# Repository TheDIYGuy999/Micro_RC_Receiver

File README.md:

# This is an ATMEL Mega328P / NRF24L01+ based 2.4GHz radio receiver
## Features:
- Compatible with this transmitter: https://github.com/TheDIYGuy999/RC_Transmitter
- Programmable with Arduino IDE
- 4 RC servo connectors
- SBUS output
- Outputs for Headlights, indicators, taillights with brake lights
- Additional switching output
- Support for self balancing robot or car with stability control (using an MPU-6050 sensor)
- Integrated TB6612FNG dual dc motor driver
- Serial header (with SBUS support)
- I2C header (for example for the supported MPU-6050)
- ICSP header for programming with Arduino IDE (use "TheDIYGuy999 328P" board definition and set brownout voltage to 1.8V)
- NRF24L01+ SMD module integrated
- very small size
- Up to 20 vehicle addresses selectable, allows to use the same remote controller for 10 vehicles
- Eagle & Gerber files are also provided, if you want to build your own receiver!

See: https://www.youtube.com/playlist?list=PLGO5EJJClJBCjIvu8frS7LrEU3H2Yz_so

New in V 1.3:
- Vehicle configuration is now stored in "vehicleConfig.h", so the main code always stays the same.
- Crude frequency hopping, if bad receiving quality is detected (needs to be improved).

New in V 1.4:
- 10 vehicle addresses instead of 5
- More vehicle configuration options
- The "BACK" button on the transmitter can now be used (if the menu screen is not displayed on the OLED) as a momentary button, for example for a horn on the vehicle. It is sent as "data.momentary1"
- SimpleTimer library replaced with my own code, which uses significantly less memory

New in V 1.5:
- Added steering mixer for semi caterpillar and caterpillar vehicles such as tanks, diggers etc.
- Channel 3 is throttle, channel 1 is steering
- More vehicle configuration options in vehicleVonfig.h
- The left caterpillar is motor 2, the right is motor 1
- Steering servo 1 can be used in parallel (for semi caterpillar vehicles or vehicles with electronic differential)

New in V 1.6:
- Added indicator lights - wired to A4 (SDA) / A5 (SCL) ports
- enabled and disabled left / right by channel 4 left / right
- disabled by turning back the steering wheel (channel 1) - just like a real car
- hazard lights (all indicators flashing), if no connection to the transmitter

New in V 1.61:
- Battery cutoff bug fixed

New in V 1.7 (Support for board revision 1.3):
- **** TB6612FNG library update to V1.1 is required! ****
- motor driver pinout has changed in board V1.3. So we are now able to adjust the PWM frequency of motor2. This allows smooth motor operation without the typical PWM whining.
- vehicleConfig.h changed: "boardVersion" and "HP" variables added. They allow to stay compatible with older board versions. Just select the correct configuration.
- The new "HP" (High Power) board version has only one motor driver channel, because both TB6612FNG channels are wired in parallel. It's able to supply 2.4A (average) / 6.4A (peak) so we can use bigger motors. This is useful for models, which use a steering servo and don't need a second motor channel.'
- automatic radio re-initialisation after signal timeout

New in V 1.71
- Battery monitoring and cutoff triggering improved. Under load, 0.3V are now added to the battery voltage to compensate the voltage drop. This allows to set the cutoff voltage to 3.6V, even with bigger loads.
- Vehicle #7 added.

New in V 1.8
- New "engineSound" variable in "vehicleconfig.h". True means, that the servo 3 pulse signal can be switched on and off, using the  channel 2 joystick. This switches the engine sound on my "Rc Engine Sound" unit on and off.

New in V 1.9
- New vehicle specific configuration section in vehicleConfig.h. The configuration is now done entirely during compilation time.

New in V 2.0
- vehicle Config.h: New vehicleType 3 (forklift) added. Motor 2 is used as lifting motor in this case. A servo is required as steering motor.
- Beacon lights can be wired to servo channel 4. Select "beacons = true" in this case. The beacons are flashing during vehicle movement and are switching off, after the vehicle did not move for 10s.

New in V 2.1
- Sounds for a STAR WARS R2-D2 robot can now be generated on servo channel 3
- "toneOut" variable added to vehicleConfig.h. True means, that servo 3 channel is generating sounds instead of a servo signal.
- Do not enable "toneOut" and "engineSound" at the same time.
- Note: the Arduino tone() function is blocking. So don't play sounds while driving ;-)

New in V 2.2
- **** TB6612FNG library update to V1.2 is required! **** https://github.com/TheDIYGuy999/TB6612FNG
- **** The PID library is required! **** https://github.com/br3ttb/Arduino-PID-Library/
- Support for self balancing (inverted pendulum, segway) vehicles. See: https://www.youtube.com/watch?v=zse9-l2Yo3Y)
- A MPU-6050 accelerometer & gyro module is used for the balancing data communication via SDA & SCL
- Note, that the receiver will not work, if your vehicleType is 4 (balancing) and no MPU-6050 is connected!
- Do not enable "balancing" and "indicators" at the same time.

New in V 2.21
- Gyro drift calibration bug fixed
- Changed the balancing controller refresh rate to 125Hz to reduce jitter on a 8MHz MCU. Reason: one program loop takes 4 - 7ms, so we can't use a time base of 4ms (=250Hz).

New in V 2.3
- MRSC (Micro RC Stability Control) added. This functionality is similar to the Traxxas TSM or ESC. See: https://www.youtube.com/watch?v=IPve7QpdLBc&t=5s
- The steering servo angle is compensated in accordance with the speed, the requested steering angle and the measured yaw rate, which is coming from the MPU-6050
- Basically the mrsc() function was added. The required yaw rate is already calculated in the balancing.h, which is already existing for self balancing robots
- If you want to use this functionality, you have to set the vehicleType to 5 in the vehicleConfig.h. Please note, that the receiver will not work, if no MPU-6050 is connected and the vehicleType is set to 4 or 5!

New in V 2.31
 - MRSC gain factor now depending on the potentiometer 1 value on the transmitter
 - Allows to fine adjust the MRSC during driving, depending on the requirements of the street surface
 - Note, that you need to connect a potentiometer to the analog input A6 of your transmitter!
 
 New in V 2.32
 - Flickering headlights bug in vehicleType 5 fixed
 - The accelerometer vectors are not processed anymore in vehicleType 5. This is only required for the self balancing robot (vehicleType 4)
 
 New in V 2.4
 - The I2C bus is scanned for an MPU-6050 sensor during the setup() sequence. The vehicleType is automatically changed to 0 (car without MRSC), if no sensor is detected.
 - This means, that a car with vehicleType 5 (MRSC Stability Control) can now also be used without an MPU-6050 plugged in.
 - Note, that the self balancing mode (vehicleType 4) always requires an MPU-6050. Otherwise the receiver will not start.
 
 New in V 2.41
 - The "indicators" variable is now locked and can't be enabled, if the SDA and SCL pins are in use for the MPU-6050 sensor. This is the case in vehicleMode 4 and 5.
 
 New in V 2.5
 - The MRSC stability control is now also working for cars without a steering servo
 - Code was added to control a DC steering motor (as found in cheap RC cars) in accordance with the MPU-6050 yaw rate
 - This is for example very useful for Coke Can Cars. See: https://www.youtube.com/watch?v=jr5yYBal3vk
 
 New in V 2.6
 - The MRSC stability control can now be used with transmitters without gain adjustment potentiometer
 - The following optional parameters in the vehicleConfig.h allow to use a fixed gain: MRSC_FIXED, mrscGain
 - Allows to add an MPU-6050 gyro to every vehicle. So we always have a closed loop steering control, even without a proper servo with potentiometer feedback
 - On the "Non-High-Power" receiver model, 0.3V battery voltage are not added anymore during driving. This is not useful, if there is not much current draw.
 
 New in V 2.7
 - The MRSC stability control gain adjustment knob can now be linked to servo CH4, if "potentiometer1" is set to "true" in vehicleConfig.h
 - This is useful, if an external MRSC stability control unit for 3 pin servos is used. See: https://github.com/TheDIYGuy999/MRSC_Adapter_3Pin_Servo
 - Servo CH4 is wired to pin 5 in this case. This allows to adjust the MRSC gain on the transmitter, just as with the internal MRSC stability control
 
 New in V 2.8
 - Added support for differential thrust controlled airplanes
 - Tested with a Piper J3 CUB from Banggood
 
 New in V 2.9
 - Added TWO_SPEED_GEARBOX option for mechanical two speed gearboxes, shifted by a servo, connected to CH2, controlled by "Mode 1" button
 - Example see vehicle CONFIG_WPL_B-36
 - See video: https://www.youtube.com/watch?v=EaOJE_GU5pk&t=1s
 
 New in V 3.0
 - Added TRACTOR_TRAILER_UNLOCK option. Used to operate the tractor trailer unlocking servo
 - Press the "Back / Pulse" button to unlock your trailer
 - See vehicle "CONFIG_JJRC_Q60" for example
 - Parts for 3D printing: https://www.thingiverse.com/thing:3399449
 
 New in V 3.1
 - Added THRE_SPEED_GEARBOX option for mechanical three speed gearboxes, shifted by a servo, connected to CH2, controlled by a 3 position switch, connected to CH2 Joystick input of the transmitter. A 10k resistor is reqired between GND and the input pin as well as between the input pin and VCC
 - Three individual servo positions can be programmed: lim2L, lim2C, lim2R
 - Example see vehicle CONFIG_HG_P407
 
 New in V 3.2
 - Added the "TXO_toggle1" variable: allows to toggle the TXO pin, using the "Back / Impulse" button on the transmitter
 - Useful for example for additional lights
 - Don't activate it in combination with "TXO_momentary1". Serial is not usable, if one of these booleans is set to true
 
 New in V 3.3
 - Added experimental support for serial communication with my "Arduino RC engine sound generator for ESP32": https://github.com/TheDIYGuy999/Rc_Engine_Sound_ESP32
 - Uncomment "#define SERIAL_COMMUNICATION" in Adjustments.h of the sound generator
 - Connect pin 36 "VP"of the sound generator  to pin "TXO" of the receiver (disable "TXO_momentary1", "TXO_toggle1" & "headLights" in vehicleConfig.h)
 
 New in V 3.31
 - "headlLights" must be inactive as well in order to use serial communication!
 
 New in V 3.32
 - "data.pot1" properly initialized (cauesd an issue on the ESP32 engine sound generator)
 
 New in V 3.4
 - SBUS support added (variable "SBUS_SERIAL" in vehicleConfiguration.h
 - Channel order and comments see sendSbusCommands()
 - You need to install my SBUS library: https://github.com/TheDIYGuy999/SBUS
 - Connect your servos or what ever to pin "TXO"  (disable "TXO_momentary1", "TXO_toggle1" & "headLights" in vehicleConfig.h)
 
 New in V 3.5
 - mode1, mode2 and momentary1 properly initialised before SBUS is enabled
 
 New in V 3.6
 - "vehicleType" 1 or 2 (tracked or half tracked mode steering mixer) is now working as well, if two ESC are connected to servo pins 2 and 3. In the past, it was only usable with the internal TB6612 dual DC motor driver.
 - Also works in combination with my ESP32 Engine Sound & Light Controller (SBUS & PWM Mode)
 
 New in V 3.7
 - Steering center position separately adjustable, using "#define STEERING_3_POINT_CAL" and "lim1C". This is useful for badly designed steering linkage geometries. Example see vehicle configuration "CONFIG_WPL_B_36_MODE1"
 
 New in V 3.8:
 - 20 vehicle addresses instead of 10
 - Less RAM usage
 - 2 speed transmission not shifting while standing still. This will protect the shifting servo.

New in V 3.81:
 - Libraries comments added
 
 New in V 3.9:
 - New "#define VEHICLE_TYPE_3_WITH_ESC" option for vehicle type 3. Allows to use both TB6612 FNG motor driver channels for other stuff
 - Used in "CONFIG_MECCANO_DUMPER"

## Usage

See pictures

Newest version v1.5:

First prototype:

Receiver PCB

MPU-6050 shield PCB

(c) 2016 - 2020 TheDIYGuy999

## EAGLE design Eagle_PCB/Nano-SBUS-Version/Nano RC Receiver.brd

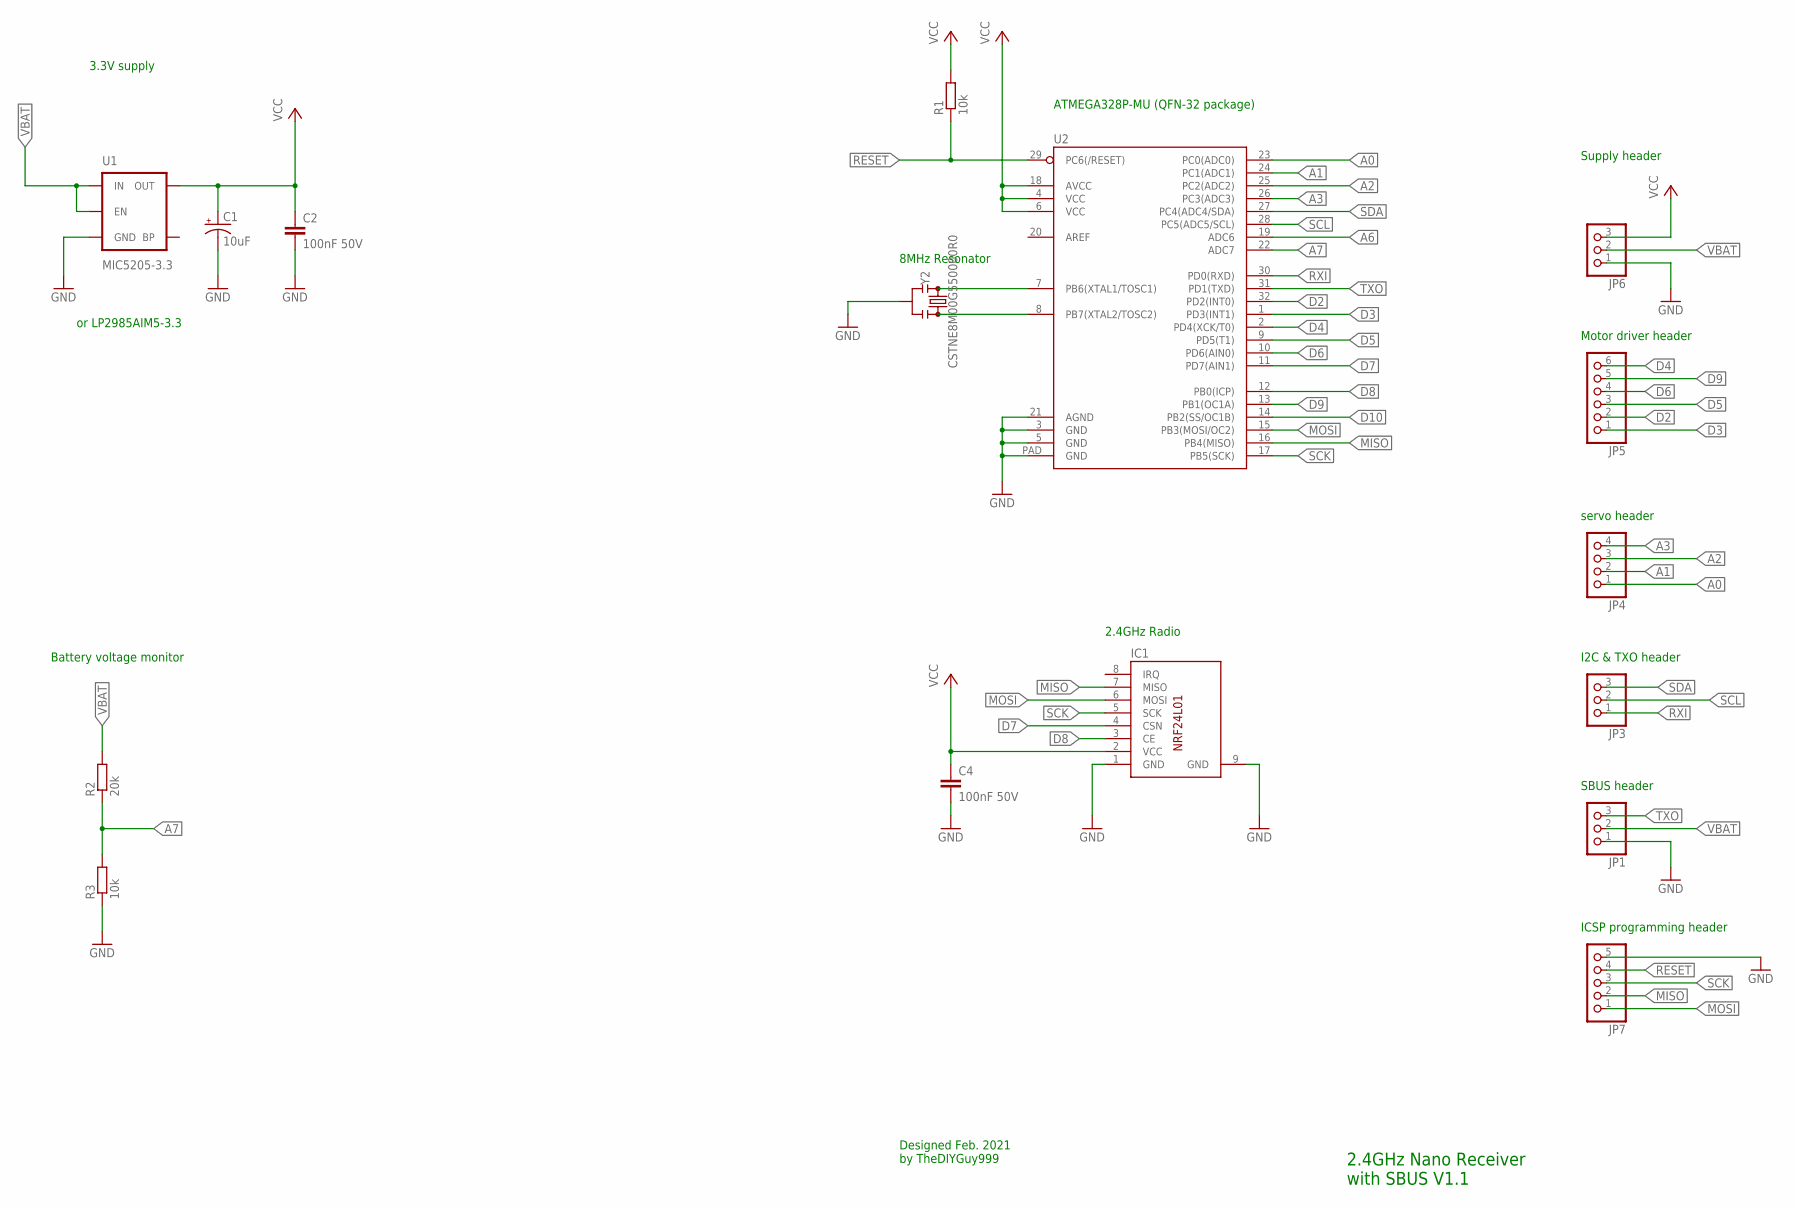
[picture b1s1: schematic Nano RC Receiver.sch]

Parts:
C1: 10uF; EIA3216
C2, C4: 100nF 50V; C0603
IC1: NRF24L01SMD_PAD; NRF24L01_SMD_PAD
JP1: PINHD-1X3SMT; 1X03_SMT
JP3, JP6: PINHD-1X31.27; 1X03_1.27
JP4: PINHD-1X41.27; 1X04_1.27
JP5: PINHD-1X61.27; 1X06_1.27
JP7: PINHD-1X51.27; 1X05_1.27
R1, R3: 10k; R0603
R2: 20k; R0603
U1: MIC5205-3.3; SOT23-5
U2: ATMEGA328P_MLFMLF32; MLF32-PAD
Y2: CSTNE8M00G550000R0; RESONATOR-SMD-3.2X1.3

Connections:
A0: JP4.1, U2.23 (PC0(ADC0))
A1: JP4.2, U2.24 (PC1(ADC1))
A2: JP4.3, U2.25 (PC2(ADC2))
A3: JP4.4, U2.26 (PC3(ADC3))
A6: U2.19 (ADC6)
A7: R2.1, R3.2, U2.22 (ADC7)
D2: JP5.2, U2.32 (PD2(INT0))
D3: JP5.1, U2.1 (PD3(INT1))
D4: JP5.6, U2.2 (PD4(XCK/T0))
D5: JP5.3, U2.9 (PD5(T1))
D6: JP5.4, U2.10 (PD6(AIN0))
D7: IC1.4 (CSN), U2.11 (PD7(AIN1))
D8: IC1.3 (CE), U2.12 (PB0(ICP))
D9: JP5.5, U2.13 (PB1(OC1A))
D10: U2.14 (PB2(SS/OC1B))
GND: C1.C (-), C2.2, C4.2, IC1.1 (GND), IC1.9 (GND), JP1.1, JP6.1, JP7.5, R3.1, U1.2 (GND), U2.3 (GND), U2.5 (GND), U2.21 (AGND), U2.PAD (GND), Y2.2
MISO: IC1.7 (MISO), JP7.2, U2.16 (PB4(MISO))
MOSI: IC1.6 (MOSI), JP7.1, U2.15 (PB3(MOSI/OC2))
RESET: JP7.4, R1.1, U2.29 (PC6(/RESET))
RXI: JP3.1, U2.30 (PD0(RXD))
SCK: IC1.5 (SCK), JP7.3, U2.17 (PB5(SCK))
SCL: JP3.2, U2.28 (PC5(ADC5/SCL))
SDA: JP3.3, U2.27 (PC4(ADC4/SDA))
TOSC1: U2.7 (PB6(XTAL1/TOSC1)), Y2.1
TOSC2: U2.8 (PB7(XTAL2/TOSC2)), Y2.3
TXO: JP1.3, U2.31 (PD1(TXD))
VBAT: JP1.2, JP6.2, R2.2, U1.1 (IN), U1.3 (EN)
VCC: C1.A (+), C2.1, C4.1, IC1.2 (VCC), JP6.3, R1.2, U1.5 (OUT), U2.4 (VCC), U2.6 (VCC), U2.18 (AVCC)

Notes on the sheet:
3.3V supply
2.4GHz Radio
2.4GHz Nano Receiver with SBUS V1.1
Designed Feb. 2021 by TheDIYGuy999
8MHz Resonator
or LP2985AIM5-3.3
Battery voltage monitor
ICSP programming header
servo header
SBUS header
I2C & TXO header
Motor driver header
Supply header
ATMEGA328P-MU (QFN-32 package)

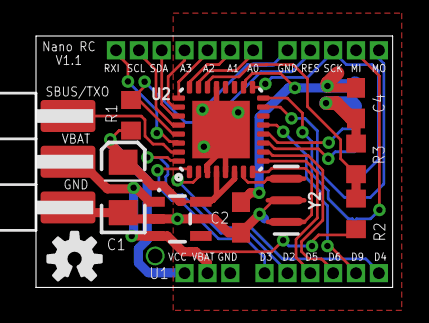
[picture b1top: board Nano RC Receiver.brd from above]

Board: 2 copper layers, 19.8 x 14.0 mm, 17 parts (1 on the bottom side), 26 nets.

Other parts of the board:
LOGO2: OSHW-LOGOS; OSHW-LOGO-S

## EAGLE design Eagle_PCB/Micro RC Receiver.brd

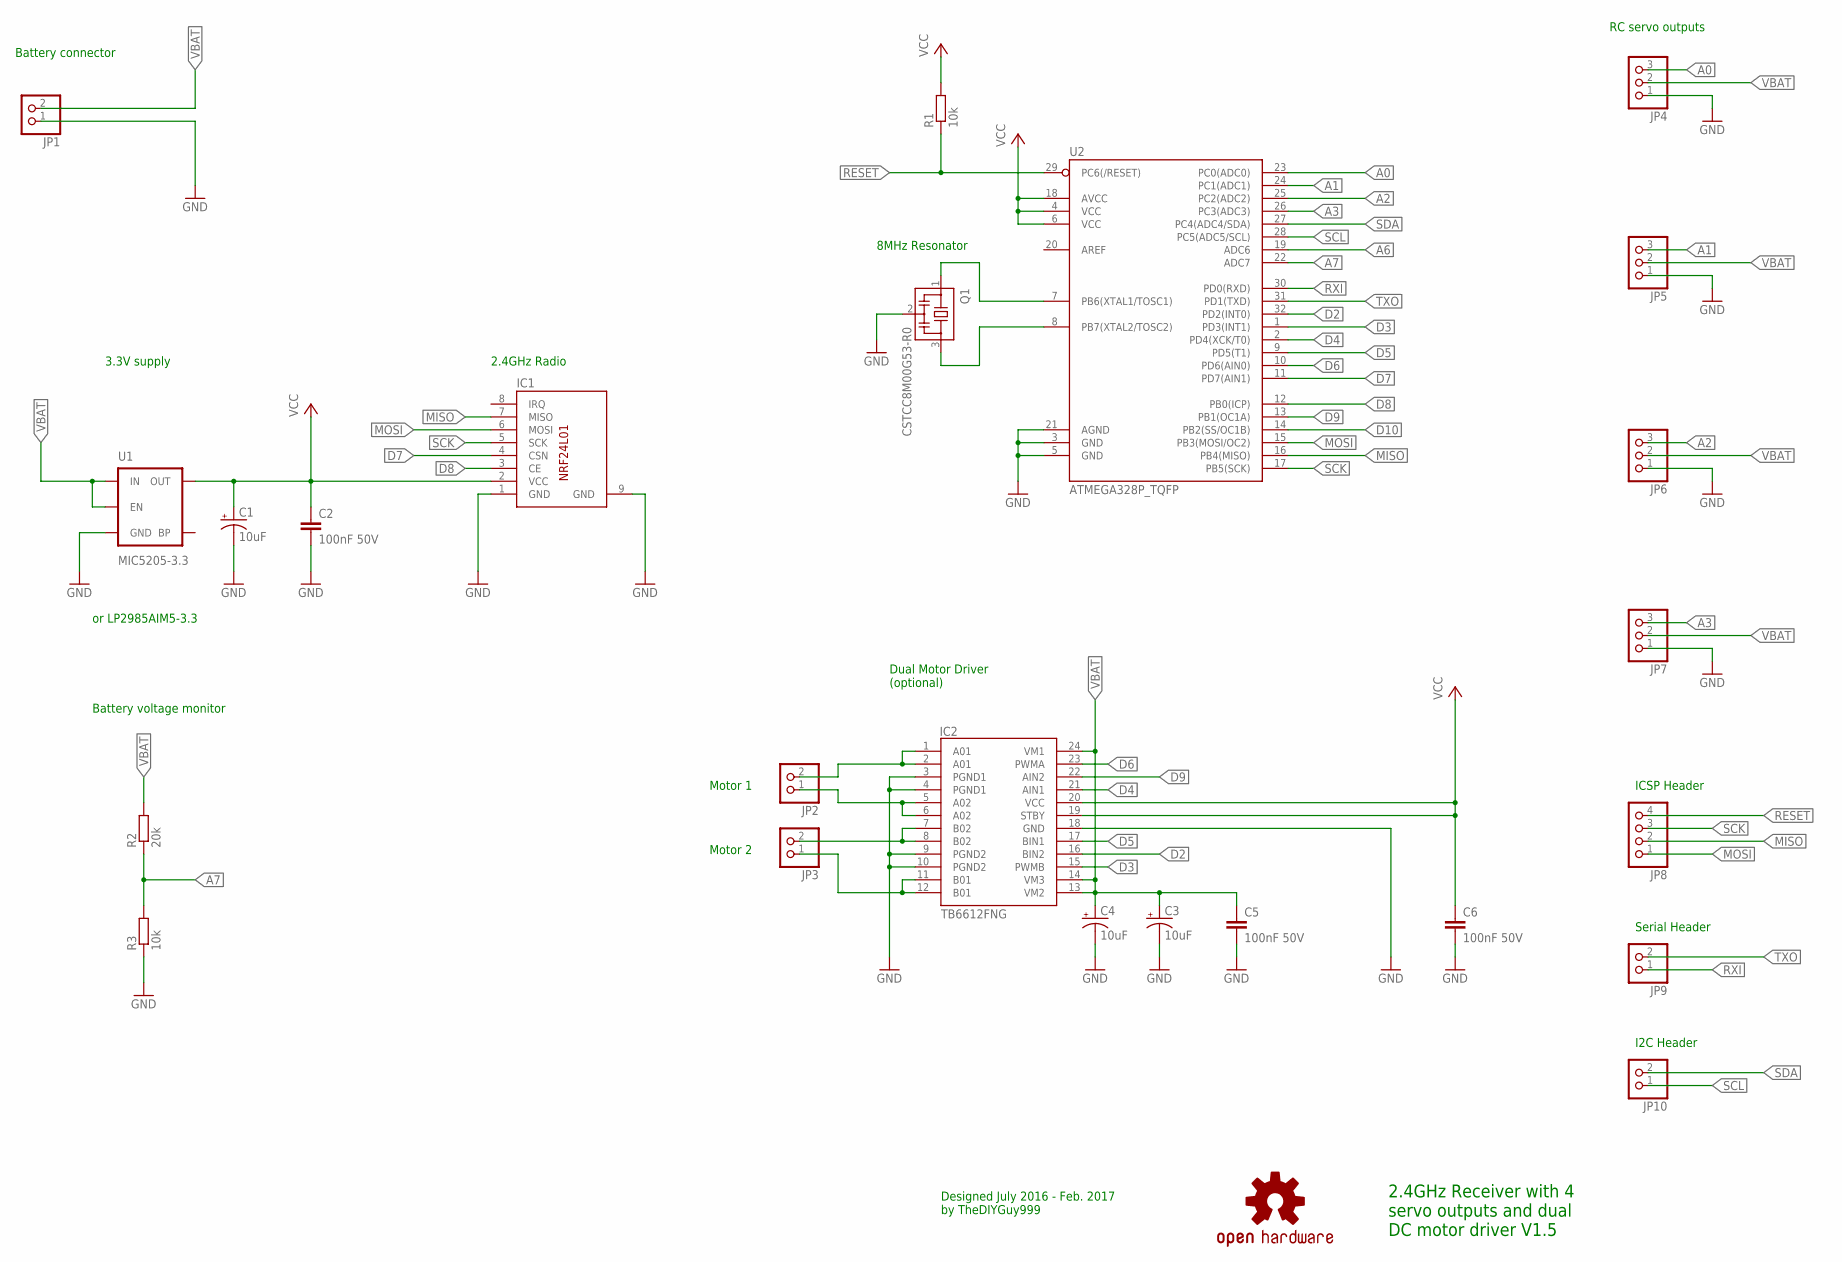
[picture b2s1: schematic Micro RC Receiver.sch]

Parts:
C1, C3, C4: 10uF; EIA3216
C2, C5, C6: 100nF 50V; C0805
IC1: NRF24L01SMD; NRF24L01_SMD
IC2: TB6612FNG; SSOP24
JP1, JP2, JP3, JP9, JP10: PINHD-1X2; 1X02
JP4, JP5, JP6, JP7: PINHD-1X3; 1X03
JP8: PINHD-1X4; 1X04
LOGO1: OSHW-LOGOS; OSHW-LOGO-S
Q1: CSTCC8M00G53-R0; CSTCC
R1, R3: 10k; R0805
R2: 20k; R0805
U1: MIC5205-3.3; SOT23-5
U2: ATMEGA328P_TQFP; TQFP32-08

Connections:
A0: JP4.3, U2.23 (PC0(ADC0))
A1: JP5.3, U2.24 (PC1(ADC1))
A2: JP6.3, U2.25 (PC2(ADC2))
A3: JP7.3, U2.26 (PC3(ADC3))
A6: U2.19 (ADC6)
A7: R2.1, R3.2, U2.22 (ADC7)
D2: IC2.16 (BIN2), U2.32 (PD2(INT0))
D3: IC2.15 (PWMB), U2.1 (PD3(INT1))
D4: IC2.21 (AIN1), U2.2 (PD4(XCK/T0))
D5: IC2.17 (BIN1), U2.9 (PD5(T1))
D6: IC2.23 (PWMA), U2.10 (PD6(AIN0))
D7: IC1.4 (CSN), U2.11 (PD7(AIN1))
D8: IC1.3 (CE), U2.12 (PB0(ICP))
D9: IC2.22 (AIN2), U2.13 (PB1(OC1A))
D10: U2.14 (PB2(SS/OC1B))
GND: C1.C (-), C2.2, C3.C (-), C4.C (-), C5.2, C6.2, IC1.1 (GND), IC1.9 (GND), IC2.3 (PGND1), IC2.4 (PGND1), IC2.9 (PGND2), IC2.10 (PGND2), IC2.18 (GND), JP1.1, JP4.1, JP5.1, JP6.1, JP7.1, Q1.2, R3.1, U1.2 (GND), U2.3 (GND), U2.5 (GND), U2.21 (AGND)
MISO: IC1.7 (MISO), JP8.2, U2.16 (PB4(MISO))
MOSI: IC1.6 (MOSI), JP8.1, U2.15 (PB3(MOSI/OC2))
unnamed: Q1.3, U2.8 (PB7(XTAL2/TOSC2))
unnamed: Q1.1, U2.7 (PB6(XTAL1/TOSC1))
unnamed: IC2.11 (B01), IC2.12 (B01), JP3.1
unnamed: IC2.7 (B02), IC2.8 (B02), JP3.2
unnamed: IC2.5 (A02), IC2.6 (A02), JP2.1
unnamed: IC2.1 (A01), IC2.2 (A01), JP2.2
RESET: JP8.4, R1.1, U2.29 (PC6(/RESET))
RXI: JP9.1, U2.30 (PD0(RXD))
SCK: IC1.5 (SCK), JP8.3, U2.17 (PB5(SCK))
SCL: JP10.1, U2.28 (PC5(ADC5/SCL))
SDA: JP10.2, U2.27 (PC4(ADC4/SDA))
TXO: JP9.2, U2.31 (PD1(TXD))
VBAT: C3.A (+), C4.A (+), C5.1, IC2.13 (VM2), IC2.14 (VM3), IC2.24 (VM1), JP1.2, JP4.2, JP5.2, JP6.2, JP7.2, R2.2, U1.1 (IN), U1.3 (EN)
VCC: C1.A (+), C2.1, C6.1, IC1.2 (VCC), IC2.19 (STBY), IC2.20 (VCC), R1.2, U1.5 (OUT), U2.4 (VCC), U2.6 (VCC), U2.18 (AVCC)

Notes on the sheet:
Motor 2
Motor 1
Dual Motor Driver (optional)
Battery connector
3.3V supply
2.4GHz Radio
RC servo outputs
2.4GHz Receiver with 4 servo outputs and dual DC motor driver V1.5
Designed July 2016 - Feb. 2017 by TheDIYGuy999
Serial Header
ICSP Header
I2C Header
8MHz Resonator
or LP2985AIM5-3.3
Battery voltage monitor

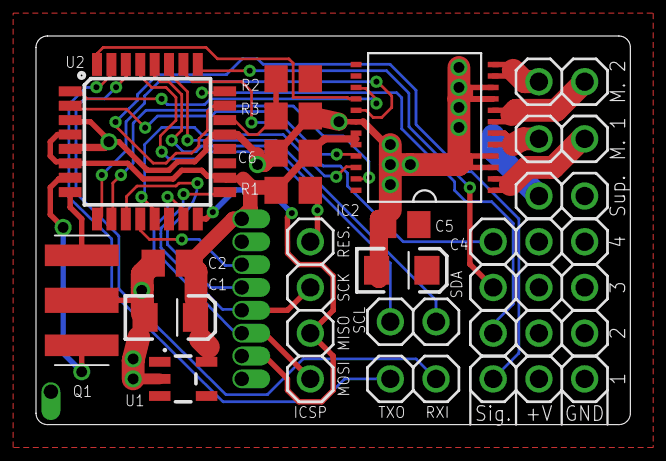
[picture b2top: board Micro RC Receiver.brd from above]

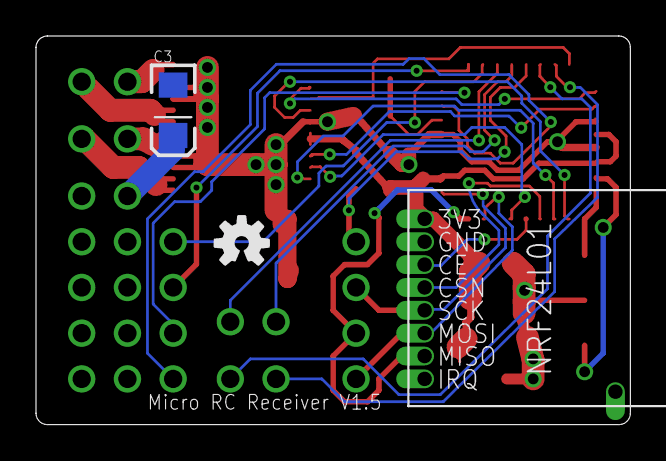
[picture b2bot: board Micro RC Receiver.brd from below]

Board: 2 copper layers, 33.0 x 21.6 mm, 25 parts (3 on the bottom side), 30 nets.

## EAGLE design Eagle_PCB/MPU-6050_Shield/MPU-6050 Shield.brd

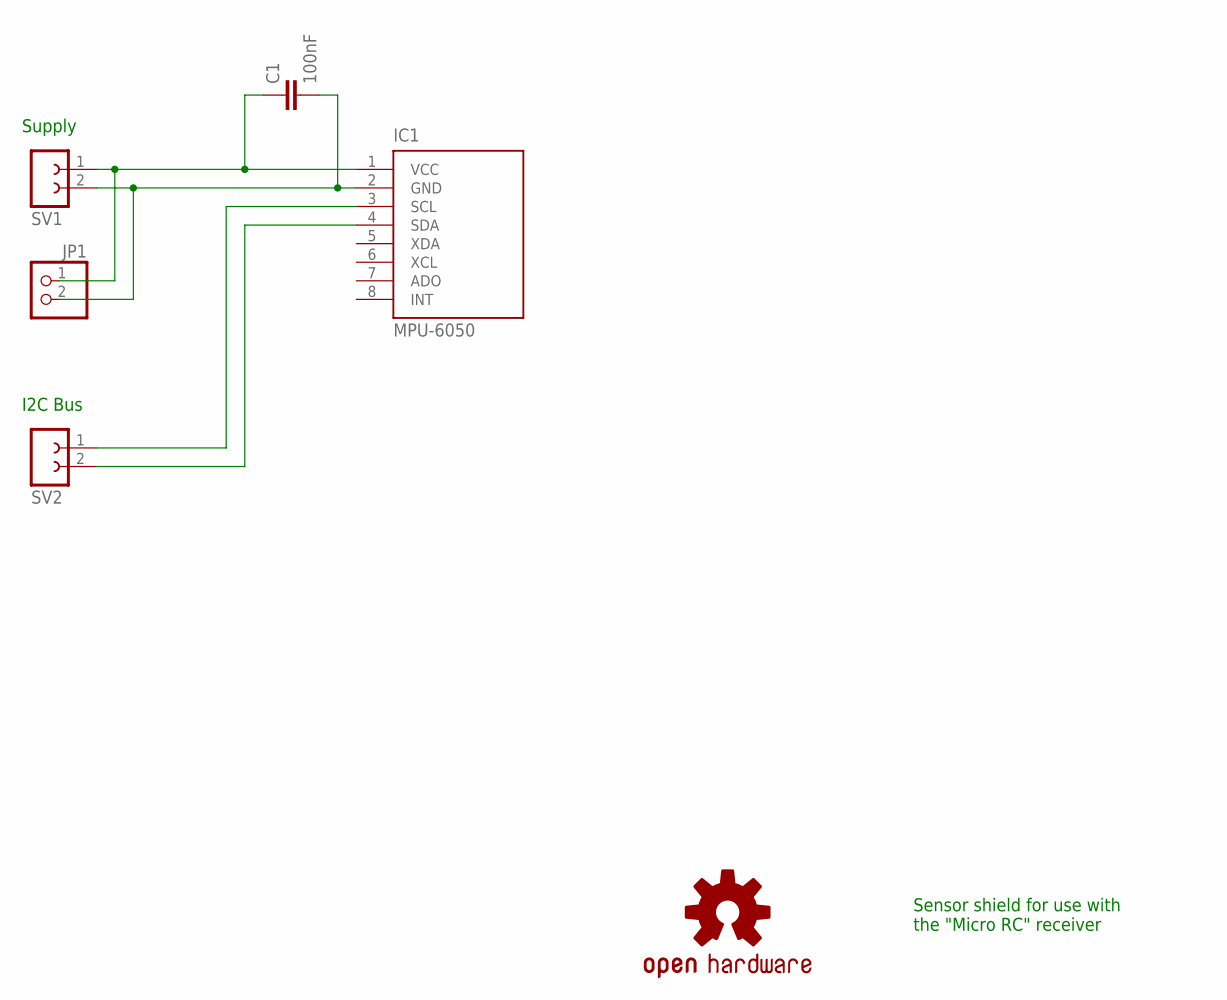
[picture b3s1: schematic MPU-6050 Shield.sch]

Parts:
C1: 100nF; C0805
IC1: MPU-6050; MPU-6050_GY521
JP1: PINHD-1X2; 1X02
LOGO1: OSHW-LOGOS; OSHW-LOGO-S
SV1, SV2: FE02-1

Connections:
GND: C1.2, IC1.2 (GND), JP1.2, SV1.2
unnamed: IC1.3 (SCL), SV2.1
unnamed: IC1.4 (SDA), SV2.2
VCC: C1.1, IC1.1 (VCC), JP1.1, SV1.1

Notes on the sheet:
Supply
I2C Bus
Sensor shield for use with the "Micro RC" receiver

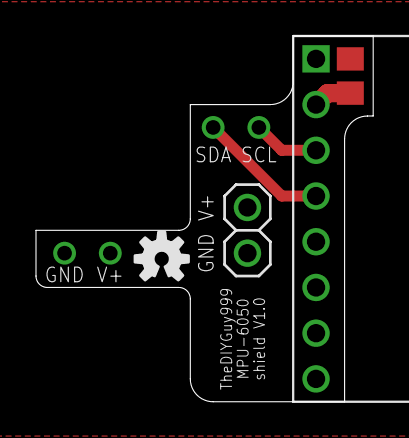
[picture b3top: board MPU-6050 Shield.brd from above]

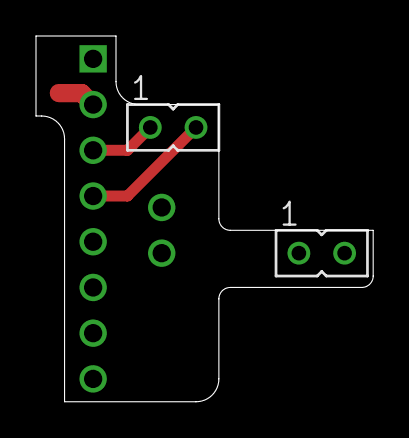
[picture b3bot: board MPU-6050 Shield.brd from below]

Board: 2 copper layers, 18.7 x 20.3 mm, 6 parts (2 on the bottom side), 4 nets.

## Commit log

2016-07-26 Create test
2016-07-27 Typo
2016-07-27 additional comments
2016-08-09 Board optimized
2016-09-13 Variant for Dodge Challenger with taillights & brake lights
2016-09-18 Variant for Porsche 911 GT3 RS 4.0
2016-09-22 Multiplayer fix
2016-10-02 New vehicle specific configuration, crude frequency hopping
2016-10-04 New V1.4
2016-10-09 V1.5 with caterpillar steering mixer
2016-10-09 V1.6 Indicator lights added
2016-11-05 V1.61: battery cutoff bug fixed
2016-11-05 Coke Can Car configuration added
2016-11-29 V1.7: support for board V1.3 and "High Power" board variant
2016-11-30 Create HP Version
2016-11-30 V 1.3 HP (High Power)
2016-11-30 V 1.3
2016-12-11 V1.71: battery cutoff triggering improved
2017-01-12 V1.8: Engine sound control option added
2017-01-29 V1.9: Vehicle configuration done during compilation time
2017-02-23 V1.4
    GND plane and decoupling improved
2017-02-23 V2.0: forklift mode and beacons added
2017-03-04 V2.1: sounds for STAR WARS R2-D2 added
2017-04-03 V2.2: support for self balancing vehicles added
2017-04-11 V. 2.21: Self balancing optimized
2017-08-08 Bill of Material added
2017-10-08 V2.21: more vehicles added
2017-10-08 V2.3: MRSC (Micro RC Stability Control) ESC added
    MPU-6050 required
2017-10-15 MRSC gain adjustment potentiometer added
2017-10-29 V2.32: Flickering headlights bug in vehicleType 5 fixed
2017-11-01 V2.4: MPU-6050 auto detection
2017-11-05 V2.41: Indicators variable now locked
2017-11-12 Pictures added
2017-12-05 MPU-6050 shield Eagle PCB added
2017-12-08 V2.5: MRSC now also working with DC steering motor
2018-02-04 Receiver Labels added
2018-02-04 STL housing data for 3D printing added
2018-02-04 STL data for 3D printing added
2018-02-11 BOM typo fixed
2018-04-02 V.2.6: optional MRSC gain potentiometer override
2018-04-10 V2.7: Gain adjustment pot can be linked to servo CH4
2018-08-26 V2.8: support for differential thrust controlled planes
2018-11-06 V2.9: support for mechanical 2 speed gearbox control
2019-02-26 New in V3.0: tractor trailer unlocking option added
2019-04-14 V3.0: Vehicles added
2019-09-24 V3.1: Added THRE_SPEED_GEARBOX option
    For 3 speed transmissions, controlled by a 3 position switch
2019-11-09 V 3.2: added "TXO_toggle1" variable (see changelog)
2019-12-27 v3.3: serial communication for ESP32 engine sound added
2019-12-28 v3.31: headlight need to be disabled as well for serial communication
2020-01-04 v3.32: minor bug fixed
2020-04-10 V1.5: board slightly optimised, Gerbers included
2020-04-11 v3.4: SBUS support added
2020-04-13 Lightweight version added
2020-05-23 Housings with clips added
2020-05-24 current pictures added
2020-10-07 v3.5: initialisation improved
2020-11-01 v3.6: dual ESC steering mixer added (see changelog)
2020-12-21 V3.7: Steering center position separately adjustable
2021-01-03 v3.8: 20 vehicle addresses etc.
2021-02-11 v3.81: libraries comments added
2021-04-02 Nano SBUS board added
2022-04-22 v3.9: new VEHICLE_TYPE_3_WITH_ESC option
2022-10-03 new ESC_MICROSECONDS option
2024-02-13 forklift version added
2024-02-15 Forklift version optimized

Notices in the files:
parts and their libraries:
SparkFun-Aesthetics: Licensing: Creative Commons ShareAlike 4.0 International - https://creativecommons.org/licenses/by-sa/4.0
